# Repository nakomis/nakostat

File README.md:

# Nakostat

## Support

If you find this useful, please consider buying me a coffee:

<!-- toc -->

- [Hardware](#hardware)
- [Architecture](#architecture)
- [Repo layout](#repo-layout)
- [Quick start](#quick-start)
- [Toolchain versions](#toolchain-versions)
- [Lint and format](#lint-and-format)
- [Deployment versions](#deployment-versions)
- [Related repos](#related-repos)
- [Licence](#licence)
- [Support](#support)

<!-- tocstop -->

A DIY smart thermostat built after the Nest thermostat and Heatlink both failed. Replaces both with a Raspberry Pi touch-screen UI, an ESP32 boiler relay controller, AWS IoT Core, and an Alexa thermostat skill.

The heatlink's circuit boards ([`pcb/heatlink/`](pcb/heatlink/)) were manufactured and assembled by
[PCBWay](https://www.pcbway.com), who sponsored the first batch.

## Hardware

| Device | Role |
|--------|------|
| Raspberry Pi 5 + RC070S 7" touch | Touch-screen UI (1024×600, egui) |
| ENS160+AHT21 | Temperature, humidity, CO₂/eCO₂/TVOC |
| ESP32-S3 heatlink | Boiler relay controller (ESP-IDF, Fleet OTA) |
| 3-way rotary switch | Physical override: auto / off / on |
| Amazon Echo | Voice control via Alexa thermostat skill |

## Architecture

```
 Pish (dial, separate repo) ─pish/setpoint─┐
 Web (nakostat.nakomis.com) ─API─► api/{setpoint,mode,schedule} ─┤
 Alexa Smart Home skill ─Lambda─► api/{setpoint,mode} ───────────┤
                                                                 ▼
          Pi sensor daemon (the brain: schedule, override, hysteresis)
             │ demand every 30 s, set_schedule          ▲ status
             ▼                                           │
     nakostat/nakostat-heatlink/commands      …/status, …/responses
             │                                           │
          Heatlink (ESP32-S3, ESP-IDF, Fleet OTA) ── relay ── boiler ROOM STAT/TIMER (230 V)
             ▲
          3-way switch (on / auto / off); falls back to a local schedule if demand stops
```

Contracts (topics, payloads): `docs/superpowers/specs/2026-10-19-heatlink-v2-prototype-design.md`.

## Repo layout

| Directory | Contents |
|-----------|----------|
| `3d/` | Printed enclosure models |
| `docs/` | Architecture diagrams and notes |
| `embedded/pi/` | Rust/egui touch UI and sensor daemon |
| `embedded/esp32/heatlink/` | ESP-IDF heatlink firmware (boiler relay, switch, fallback schedule); see its [README](embedded/esp32/heatlink/README.md) |
| `githooks/` | Pre-commit hooks |
| `infra/` | AWS CDK stacks |
| `pcb/` | PCB designs |
| `scripts/` | Helper scripts |
| `web/` | React dashboard (nakostat.nakomis.com) |

## Quick start

```bash
# Install git hooks
bash scripts/install-hooks.sh
```

## Toolchain versions

Every toolchain is pinned in [`.tool-versions`](.tool-versions), which is the single source of truth for local development and CI:

| Tool | Used by | How CI reads it |
|------|---------|-----------------|
| `nodejs` | `infra/`, `web/` | `actions/setup-node` with `node-version-file: .tool-versions` |
| `pnpm` | `infra/`, `web/` | `pnpm/action-setup` reads `packageManager` in `infra/package.json` and `web/package.json`; the **Toolchain pins** job fails if that disagrees with `.tool-versions` |
| `python` | heatlink host tests (`embedded/esp32/heatlink/tests/`) | `actions/setup-python` with `python-version-file: .tool-versions` |
| `rust` | `embedded/pi/sensor-daemon/` | the `rust` line is passed to `dtolnay/rust-toolchain` |

With [asdf](https://asdf-vm.com/) (`nodejs`, `pnpm`, `python` and `rust` plugins) run `asdf install` in the repo root; with [mise](https://mise.jdx.dev/), `mise install`. The heatlink firmware builds with ESP-IDF 5.5 (installed with Espressif's own `install.sh`, not asdf); its host tests need pytest from [`embedded/esp32/heatlink/tests/requirements.txt`](embedded/esp32/heatlink/tests/requirements.txt).

To bump a tool, change `.tool-versions` (and, for pnpm, `packageManager` in `package.json`) in the same PR.

## Lint and format

CI gates every sub-project on lint and formatting as well as tests. Run the same checks locally before pushing:

```bash
# web/ — Biome lint + format check
cd web && pnpm lint

# infra/ — type-check, then Biome at the version infra/biome.json declares
cd infra && pnpm exec tsc --noEmit && pnpm dlx @biomejs/biome@2.4.16 ci .
# auto-fix formatting and safe lint fixes:
cd infra && pnpm dlx @biomejs/biome@2.4.16 check --write .

# embedded/pi/sensor-daemon/ — rustfmt + clippy
cd embedded/pi/sensor-daemon && cargo fmt --check && cargo clippy --all-targets -- -D warnings
```

Keep the Biome version in `infra/biome.json`'s `$schema` equal to `web/biome.json`'s; the **Toolchain pins** job checks this. The ESP32 firmware has no lint gate yet: it has no `.clang-format`, and `pio check` would download the whole ESP32 toolchain on every run.

## Deployment versions

Infra deploys record their version in the shared nakomis deployment tracker (`api.infra.nakomis.com`, defined in [nakomis-infra](https://github.com/nakomis/nakomis-infra)) under the project key `nakostat-infra`. On a push to `main` the **Compute infra version** job reads the latest sandbox version from the tracker and bumps it — a line that is exactly `--bump-major` or `--bump-minor` in the merged commit message bumps that part, otherwise the patch. The same `infra/version.json` is deployed to sandbox and then prod, and each deploy is recorded after it succeeds. Recording is non-fatal, so a tracker outage never fails a deploy.

## Related repos

- [`rotary-dial`](https://github.com/nakomis/rotary-dial) — egui thermostat dial widget (migrating into `embedded/pi/`)
- [`pish`](https://github.com/nakomis/pish) — the Pi touch-screen shell; its `nakostat` widget is the thermostat dial
- [`nakomis-fleet`](https://github.com/nakomis/nakomis-fleet) — device registry and OTA for the heatlink

## Licence

[CC0 1.0 Universal](LICENSE) — public domain dedication.

## Support

If you find this useful, please consider buying me a coffee:

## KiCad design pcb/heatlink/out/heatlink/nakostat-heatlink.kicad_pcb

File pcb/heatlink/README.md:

# Nakostat heatlink board (STAT-75)

The heatlink on one board: an ESP32-S3-MINI-1 module, a relay on the boiler's 230 V
`ROOM STAT/TIMER` pair, the 3-way override toggle, a WS2812B status LED, and, to make spare boards
reusable, an 8-way IO terminal (power, I²C and three GPIOs) and a 16-way IDC header (twelve more). It is powered over the
house USB cable. The board is generated in code, from the circuit through to the gerbers, using
tinycrypt's pipeline. `DESIGN.md` covers the parts, the circuit and the mains safety rules.

**[The component key](../../docs/heatlink-board-key.md)** explains what every numbered part does, and why it's there. The dashed orange
ring marks where the case needs a vent: above the 3.3 V regulator (U2), the warmest part.

## Build

```bash
ASDF_PYTHON_VERSION=3.11.15 python -m venv .venv
.venv/bin/pip install -r requirements.txt
mkdir -p freerouting && cp <somewhere>/freerouting-2.5.0.jar freerouting/   # Java via asdf (25)
./fetch_parts.sh                       # only if footprints/ is missing or a part is added
.venv/bin/python build.py --route      # full router log: /tmp/claude-501/heatlink-board-route.log
.venv/bin/python -m pytest
```

`build.py` writes these to `out/heatlink/`:

- `nakostat-heatlink.kicad_pcb`, with its `.kicad_pro` and `.kicad_dru` (the mains rules)
- `drc.json`
- `bom-jlcpcb.csv` and `bom-pcbway.csv`
- `cpl.csv`
- `nakostat-heatlink-gerbers.zip`
- the top and bottom renders
- `pins.h`
- `nakostat-heatlink-key.png` and `docs/heatlink-board-key.md` (the text lives in `board/key.py`; after editing it,
  `.venv/bin/python -m board.key` redraws both from the existing render without a rebuild)

It writes the fab files only when KiCad's DRC reports no errors and no unconnected items. Those
checks include the 8 mm mains spacing. `--step` also fetches the 3D models and writes
`nakostat-heatlink.step` and a 3D render, which the case design needs.

## Made by PCBWay (sponsored)

The first five boards (November 2026) were manufactured and assembled by
[PCBWay](https://www.pcbway.com), who sponsored the build: they covered the boards, the parts and the
assembly. The files here aren't tied to them; the same gerbers and placement file, with
`bom-jlcpcb.csv`, also work at JLCPCB.

## Ordering

The same files work for both fabs. Only the BOM differs.

| | PCBWay | JLCPCB |
|---|---|---|
| Gerbers | `nakostat-heatlink-gerbers.zip` | same |
| BOM | `bom-pcbway.csv` (manufacturer + part number) | `bom-jlcpcb.csv` (LCSC numbers) |
| Placement | `cpl.csv` | same |

- 2 layers, 1.6 mm, **ENIG**, **black** mask, white silkscreen.
- Assembly is top side only. Five parts are through-hole: K1 (relay), J2 and J3 (terminal blocks),
  J4 (IDC header) and SW2 (toggle switch).
- The module's antenna **overhangs the board edge by 5.05 mm on purpose**. If the engineering
  review asks, say the overhang is intended.
- The board carries 230 V between J2 and the relay contacts. There is no ground pour in that area,
  and it is marked on both silkscreens.
- Check the rotations of U1, J1, J2, J3, J4, K1 and SW2 in the fab's placement preview.

## Before the first power-up

- **Check the USB cable's pinout with a meter:** 1 VBUS, 2 D−, 3 D+, 4 CC, 5 GND. A reversed VBUS
  trips the resettable fuse, but the data lines have no protection against a wrong cable.
- **Bench-test first with no mains connected.** Use the same steps as the prototype
  (`docs/heatlink-prototype-wiring.md`): the relay should click on demand, and the toggle should
  override it.
- **Wire the boiler with the power off at the spur.** L and SL go to J2 in place of the link wire.
  Fit bootlace ferrules to the flex, and clamp it in the gland so no pull reaches J2.
- **Use nylon screws in the two mains-end holes (H1, H2).** A metal M3 screw and washer in H2 would
  sit about 2.9 mm from J2, inside the board's own 3 mm rule.
- **Use a reputable, certified USB charger.** Its isolation is the real barrier between the mains
  and everything on the low-voltage side, including J3 and J4.
- **Keep loads on J3 and J4 small:** about 100 mA from 3V3 and 150 mA from 5V. The 3V3 regulator
  runs warm at sustained loads, and the 500 mA polyfuse is shared with the relay and the module,
  so a short on a header's 5V pin drops the heating control until it's removed.
- **House it in a flame-retardant enclosure** (UL94 V-0, e.g. a bought ABS or PC box, or a V-0
  filament), not PETG or ASA, because the case holds the 230 V terminals.

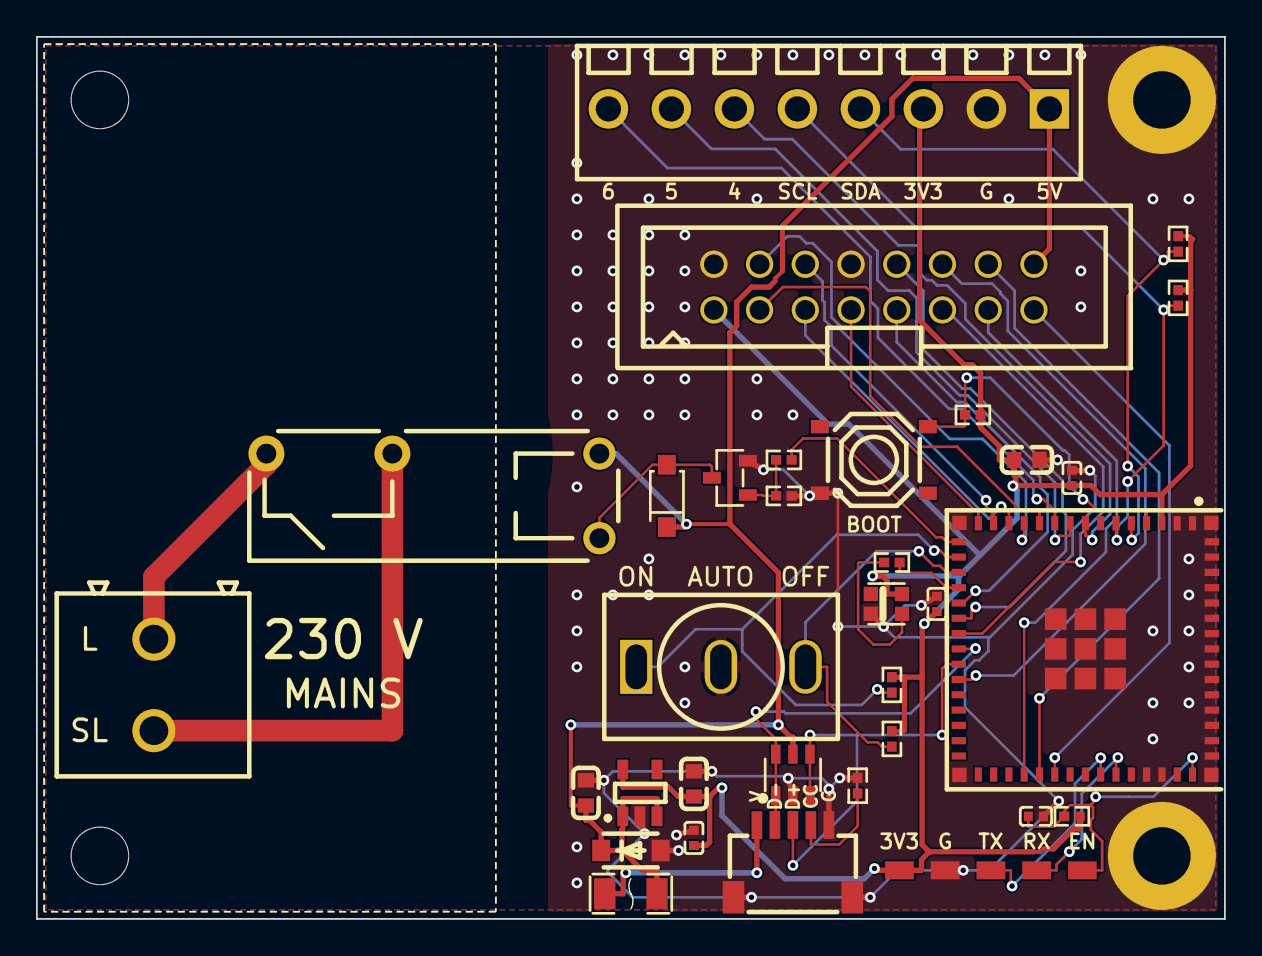
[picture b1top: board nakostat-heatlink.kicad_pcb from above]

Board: 2 copper layers, 66.0 x 49.0 mm, 38 parts (1 on the bottom side), 37 nets.

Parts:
ART1: ART1
C1, C2, C4: 10uF; C0603
C3, C5, C8: 100nF; C0402
C6: 1uF; C0402
D1: WS2812B-2020-V6; LED-SMD_4P-L2.2-W2.0-P1.00_WS2815C-2020-4P
D2: SMF5.0A; SOD-123F_L2.8-W1.8-LS3.7-RD
D3: 1N4148W; SOD-123F_L2.7-W1.6-LS3.8-RD
F1: 500mA PTC; F1206
H1, H2: M3 hole, unplated; MountingHole_M3_3.2mm_NPTH
H3, H4: M3 hole; MountingHole_M3_3.2mm_Pad6
J1: SM05B-SRSS-G-TB; CONN-SMD_SM05B-SRSS-G-TB-LF-SN
J2: KF128-5.08-2P; CONN-TH_P5.08_KF128-5.08-2P
J3: DB125-3.5-8P-GN-S; CONN-TH_8P-P3.50_DORABO_DB125-3.5-8P-GN-S
J4: DC3-2.54-16PAS; IDC-TH_16P-P2.54_C3406
K1: HF46F/5-HS1; RELAY-TH_HF46F-XX-HS1XX-XXX
Q1: AO3400A; SOT-23-3_L2.9-W1.3-P1.90-LS2.4-BR
R1: 5k1; R0402
R2, R3, R9, R10: 10k; R0402
R4, R5: 4k7; R0402
R6: 330R; R0402
R7: 100R; R0402
R8: 100k; R0402
SW1: TS-1187A-B-A-B; SW-SMD_4P-L5.1-W5.1-P3.70-LS6.5-TL_H1.5
SW2: MTS-103 ON-OFF-ON; SW-TH_MT-0-103-A101-M200-RS
TP1: Debug pads; DebugPads_1x5_P2.54
U1: ESP32-S3-MINI-1-N8; BULETM-SMD_ESP32-S3-MINI-1-N8
U2: AP2112K-3.3TRG1; SOT-25-5_L2.9-W1.6-P0.95-LS2.8-BL
U3: USBLC6-2SC6; SOT-23-6_L2.9-W1.6-P0.95-LS2.8-BL

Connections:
+3V3: C2.1, C3.1, C4.1, C5.1, C8.1, D1.4, J3.3, J4.1, R2.2, R3.2, R4.2, R5.2, R9.2, R10.2, TP1.5, U1.3, U2.5
BUTTON: R3.1, SW1.2, U1.4
CC: J1.4, R1.1
COIL: D3.2, K1.2, Q1.3
EN: C6.1, R2.1, TP1.1, U1.45
GND: C1.2, C2.2, C3.2, C4.2, C5.2, C6.2, C8.2, D1.2, D2.2, H3.1, H4.1, J1.5, J1.6, J1.7, J3.2, J4.2, J4.8, Q1.2, R1.2, R8.2, SW1.3, SW2.2, TP1.4, U1.1, U1.2, U1.42, U1.43, U1.46, U1.47, U1.48, U1.49, U1.50, U1.51, U1.52, U1.53, U1.54, U1.55, U1.56, U1.57, U1.58, U1.59, U1.60, U1.GND, U2.2, U3.2
HDR_7: J4.3, U1.11
HDR_8: J4.4, U1.12
HDR_9: J4.5, U1.13
HDR_10: J4.6, U1.14
HDR_11: J4.7, U1.15
HDR_16: J4.9, U1.20
HDR_17: J4.10, U1.21
HDR_18: J4.11, U1.22
HDR_21: J4.12, U1.25
HDR_38: J4.13, U1.34
HDR_39: J4.14, U1.35
HDR_40: J4.15, U1.36
IO_4: J3.6, U1.8
IO_5: J3.7, U1.9
IO_6: J3.8, U1.10
IO_SCL: J3.5, R5.1, U1.6
IO_SDA: J3.4, R4.1, U1.5
LED: R6.2, U1.19
LED_DIN: D1.3, R6.1
MAINS_L: J2.2, K1.4
MAINS_SL: J2.1, K1.3
RELAY: R7.2, U1.16
RELAY_G: Q1.1, R7.1, R8.1
SW_OFF: R10.1, SW2.3, U1.18
SW_ON: R9.1, SW2.1, U1.17
UART_RX: TP1.2, U1.40
UART_TX: TP1.3, U1.39
USB_DM: J1.2, U1.23, U3.1, U3.6
USB_DP: J1.3, U1.24, U3.3, U3.4
VBUS: C1.1, D2.1, D3.1, F1.2, J3.1, J4.16, K1.1, U2.1, U2.3, U3.5
VBUS_IN: F1.1, J1.1

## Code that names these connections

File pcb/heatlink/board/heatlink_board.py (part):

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ANTENNA = -ESP32_ANTENNA[1] + ESP32_ANTENNA[3]   # 5.05 mm of overhang
MAINS_X = 28.5                         # low-voltage copper stays right of this line (8 mm rule + margin)

# GPIO choice. USB is fixed by the silicon; the relay, switch and LED take the module's inner
# edge (pads 16-19, which face the rest of the board); the button keeps GPIO0 (download strap).
# None is a strapping pin (3/45/46), a flash pin (26-32), an eFuse-dependent SPI pin (33-37) or
# an octal pin (47/48). At reset every one of them is an input, so the relay FET's 100k
# pull-down holds the relay off until the firmware drives it.
GPIO = {"RELAY": 12, "SW_ON": 13, "SW_OFF": 14, "LED": 15, "BUTTON": 0, "USB_DM": 19, "USB_DP": 20,
        "UART_TX": 43, "UART_RX": 44, "IO_SDA": 1, "IO_SCL": 2, "IO_4": 4, "IO_5": 5, "IO_6": 6,
        **{f"HDR_{n}": n for n in (7, 8, 9, 10, 11, 16, 17, 18, 21, 38, 39, 40)}}
_MODPIN = {43: "TXD0", 44: "RXD0"}
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

# J1 (house USB, tinycrypt's J1): 1 VBUS, 2 D-, 3 D+, 4 CC, 5 GND; pads 6/7 are the shell tabs.
J1_PINS = {"1": "VBUS_IN", "2": "USB_DM", "3": "USB_DP", "4": "CC", "5": "GND"}
J1_LABELS = {"1": "V", "2": "D-", "3": "D+", "4": "CC", "5": "G"}
# J2 (boiler): the permanent live in, and the switched live back to the boiler. The relay just
# joins them, so the order does not matter electrically; the labels match the boiler's wiring.
J2_PINS = {"2": "MAINS_L", "1": "MAINS_SL"}
J2_LABELS = {"2": "L", "1": "SL"}
DEBUG_PINS = {"1": "EN", "2": "UART_RX", "3": "UART_TX", "4": "GND", "5": "+3V3"}
DEBUG_LABELS = {"1": "EN", "2": "RX", "3": "TX", "4": "G", "5": "3V3"}
# J3 (IO terminal, for reuse): 5V at one end, so a stray strand from it can reach only GND (and
# the PTC limits that); 3V3 beside a GPIO does no harm. SDA/SCL have 4.7k pull-ups to 3V3. The
# GPIOs go straight to the module, as on a dev board. All five are ADC1 pins.
IO_PINS = {"1": "VBUS", "2": "GND", "3": "+3V3", "4": "IO_SDA", "5": "IO_SCL", "6": "IO_4", "7": "IO_5",
           "8": "IO_6"}
IO_LABELS = {"1": "5V", "2": "G", "3": "3V3", "4": "SDA", "5": "SCL", "6": "4", "7": "5", "8": "6"}
# J4 (16-way boxed IDC header, 2.54 mm): a ground between the signal groups, as ribbon practice
# has it; 3V3 and GND at pin 1-2, 5V at pin 16. Odd pins are the row on the key side.
HDR_PINS = {"1": "+3V3", "2": "GND", "3": "HDR_7", "4": "HDR_8", "5": "HDR_9", "6": "HDR_10",
            "7": "HDR_11", "8": "GND", "9": "HDR_16", "10": "HDR_17", "11": "HDR_18", "12": "HDR_21",
            "13": "HDR_38", "14": "HDR_39", "15": "HDR_40", "16": "VBUS"}
HDR_LABELS = {n: {"+3V3": "3V3", "GND": "G", "VBUS": "5V"}.get(net, net[4:]) for n, net in HDR_PINS.items()}
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    c.connect("VBUS_IN", (f1, "1"))
    c.connect(vbus, (f1, "2"), (d2, "1"))            # D2 pad 1 = cathode
    c.connect(gnd, (d2, "2"))
    c.connect("USB_DM", (u3, "1"), (u3, "6"), (u1, modpin(GPIO["USB_DM"])))
    c.connect("USB_DP", (u3, "3"), (u3, "4"), (u1, modpin(GPIO["USB_DP"])))
    c.connect(vbus, (u3, "5"))
    c.connect(gnd, (u3, "2"))
    c.connect("CC", (c.add("R5K1", "R1"), "1"))
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    c.connect(gnd, (q1, "S"))
    r7, r8 = c.add("R100", "R7"), c.add("R100K", "R8")
    c.connect("RELAY_G", (q1, "G"), (r7, "1"), (r8, "1"))
    c.connect("RELAY", (r7, "2"), (u1, modpin(GPIO["RELAY"])))
    c.connect(gnd, (r8, "2"))
    for pad, net in J2_PINS.items():
        c.connect(net, (j2, pad))
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    # 3-way toggle (ON-OFF-ON): common (2) to GND, each throw to a GPIO with a 10k pull-up. The
    # middle position (neither throw) is auto.
    c.connect(gnd, (sw2, "2"))
    c.connect("SW_ON", (sw2, "1"), (u1, modpin(GPIO["SW_ON"])), (c.add("R10K", "R9"), "1"))
    c.connect("SW_OFF", (sw2, "3"), (u1, modpin(GPIO["SW_OFF"])), (c.add("R10K", "R10"), "1"))
    c.connect(v33, (c.instances["R9"], "2"), (c.instances["R10"], "2"))

    # WS2812B-2020: VDD 3V3 + 100 nF, DIN from a GPIO through 330R, DOUT unconnected.
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    cap("C100N", "C8", v33)

    # Debug pads: EN, UART0 (GPIO43/44), GND, 3V3.
    c.connect("UART_TX", (u1, modpin(GPIO["UART_TX"])))
    c.connect("UART_RX", (u1, modpin(GPIO["UART_RX"])))
    for pad, net in DEBUG_PINS.items():
        c.connect(net, (tp, pad))

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
def mains_hand_route():
    """(tracks, vias) for the two mains nets, F.Cu only: J2 -> relay contacts. MAINS_L runs up
    from J2's upper pin and across to pad 4; MAINS_SL along y = J2's lower pin to x of pad 3,
    then up. They stay at least MAINS_FUNCTIONAL apart."""
    _KEY.update({"J2": "TERM", "K1": "RELAY"})
    jl, jsl = pad_xy("J2", "2"), pad_xy("J2", "1")
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    h = Image.open(ART_PNG).size[1]
    holes = [(AT[r][0], AT[r][1], HOLE_CLEAR) for r in ("H3", "H4")]
    # and the through-hole pads that come through to the back under her: the toggle's three and
    # the relay's coil pins (silk over a pad is clipped by the fab anyway)
    _KEY.update({"SW2": "TOGGLE", "K1": "RELAY"})
    holes += [(*pad_xy("SW2", n), 1.9) for n in "123"] + [(*pad_xy("K1", n), 1.3) for n in "12"]
    return [(ART_PNG, ART_X, ART_TOP, round(h * ART_PX, 3), "back", holes)]
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
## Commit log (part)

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2026-04-24 chore: scaffold nakostat monorepo
    Directory structure, gitignore, README, CLAUDE.md, githooks, and scripts
    matching the bootboots project layout.
2026-04-24 chore: add CI, licence, updated README, and test-first policy
    - CC0 LICENSE
    - README with Support/donate section at top and bottom
    - CLAUDE.md: test-first approach, 70% coverage policy, per-language tooling
    - GitHub Actions CI: Rust/llvm-cov, CDK/Jest, React/Vitest+Playwright, ESP32/PlatformIO native
    Each job skips gracefully when the sub-project directory is empty
2026-04-25 refactor(infra): move nakostat CI role definition into GithubCiStack
2026-04-25 feat(ci): add CDK synth, sandbox and prod deploy jobs
2026-04-25 fix(ci): check out post-merge ref on PRs to test what will land on main
2026-04-26 feat(web): CloudFront SPA hosting and Cognito client for nakostat (NAKO-22)
    - WebCertStack: ACM cert for nakostat.{domain} in us-east-1 (CloudFront requirement)
    - WebStack: S3 bucket + CloudFront distribution with OAC, SPA 404→index.html routing,
    Cognito UserPoolClient referencing shared nakomis-infra pool via SSM,
    Route53 A+AAAA aliases for nakostat.sandbox.nakomis.com / nakostat.nakomis.com
    - Client ID published to SSM at /nakostat/{env}/cognito/client-id
    - 55 tests, 100% coverage
2026-04-26 feat(web): add One Dark managed login branding for nakostat client (NAKO-22)
    CloudFormation requires a clientId on CfnManagedLoginBranding, so branding
    lives here in WebStack tied to the nakostat-{env} client rather than in
    the shared AuthStack.
2026-04-26 fix(ci): bump all Node versions to 25 to match local toolchain
2026-04-26 chore(web): add open-source notice comment to index.html
2026-04-26 fix(web): remove webServer from playwright config, pass-with-no-tests in CI
2026-04-26 fix(web): add type declarations for PNG and SVG image imports
2026-04-26 fix(web): don't override OIDC credentials with AWS_PROFILE in CI
2026-04-26 fix(web): read region from env var before falling back to aws configure
2026-04-26 ci(web): verify set-config.sh against sandbox AWS in PR checks
2026-04-27 feat(web): add favicon set and webmanifest (NAKO-33)
2026-04-27 feat(infra+web): IoT rules, HTTP API, and current state panel (NAKO-30, NAKO-21, NAKO-26)
    - IotRulesStack: IoT Topic Rules routing pi/readings and esp32/status MQTT to Lambda → DynamoDB
    - ApiStack: HTTP API Gateway v2 with GET /state and GET /readings endpoints, CORS, SSM-published URL
    - CurrentStatePanel: React MUI card fetching thermostat state from the API
    - config template and set-config.sh updated to include apiUrl (graceful fallback if not yet deployed)
2026-04-27 fix(ci): always run sensor-daemon job — path filter was broken
    The if-condition used github.event.pull_request.changed_files_url which
    is an API URL, not a file path list, so contains('embedded/pi') always
    evaluated false and skipped the job on every PR.
2026-04-27 Revert "fix(ci): exclude main.rs from coverage — binary entry point is not unit-testable"
    This reverts commit e5166499ca194c7066a02e5f58c282c8feca8ac6.
2026-04-27 test(pi): add coverage for MqttPublisher error paths (NAKO-17)
    Tests for sink error propagation and MqttPublisher::new failure modes
    (missing cert, missing key, no private key in PEM) bring mqtt.rs
    coverage above 70%, satisfying the CI threshold without excluding files.
2026-04-27 ci: skip ESP32 job gracefully when project not yet initialised (NAKO-17)
2026-04-27 ci: add CI Status gatekeeper job for path-filtered checks
2026-04-27 feat(infra): API Gateway Cognito authoriser and write endpoints (NAKO-35)
    Add JWT authentication via Cognito UserPool authoriser to all API routes.
    Implement POST /setpoint handler to update boiler heating setpoint and publish
    MQTT notifications with user tracking. Implement GET /boiler-usage handler to
    query boiler on/off history with date range and source filtering. Add DynamoDB
    table (nakostat-boiler-usage-{env}) with TTL for automatic 1-year retention.
    Include comprehensive unit tests (70%+ coverage) with aws-sdk-client-mock.
2026-04-27 Trigger CI with new gatekeeper job
2026-04-27 chore(infra): update lock file for IoT Data Plane SDK
2026-04-27 fix(infra): resolve Jest/AWS SDK ESM compatibility and mock issues (NAKO-35)
    @aws-sdk/xml-builder v3.972.20 introduced @nodable/entities (pure ESM, no CJS
    build), breaking Jest's CJS runner with 'Unexpected token export'.
    Fixes:
    - Pin @aws-sdk/xml-builder to 3.972.19 via npm overrides (last version without
    @nodable/entities dependency)
    - Add transformIgnorePatterns to allow Jest to transform @aws-sdk, @smithy, and
2026-04-27 feat(infra): API Gateway Cognito authoriser and write endpoints (NAKO-35) (#20)
    * ci: add CI Status gatekeeper job for path-filtered checks
    * feat(infra): API Gateway Cognito authoriser and write endpoints (NAKO-35)
    Add JWT authentication via Cognito UserPool authoriser to all API routes.
    Implement POST /setpoint handler to update boiler heating setpoint and publish
    MQTT notifications with user tracking. Implement GET /boiler-usage handler to
    query boiler on/off history with date range and source filtering. Add DynamoDB
2026-05-03 Adds icons (#21)
2026-05-06 feat(boiler): add nakostat-boiler ESP32 firmware (STAT-13)
    Generated from esp32-bootstrap @ main with:
    - core libs: SDLogger, WifiConnect, BluetoothOTA, OTAUpdate
    - AWSAuth (SigV4 signing, credentials provider)
    - certificates scripts
    Lands at embedded/esp32/boiler/. Builds cleanly:
    pio run -e esp32s3_n16r8
2026-05-06 feat(boiler): MQTT setpoint control + relay watchdog
    First cut of the closed-loop boiler controller. Pi-side controller
    publishes thin commands ({"on": true|false}) on
    nakostat/{env}/esp32/command; ESP32 drives a relay GPIO accordingly
    and publishes JSON status on nakostat/{env}/esp32/status (on every
    command, on connect, on watchdog trip, plus a 30s heartbeat).
    - New BoilerController library wraps relay GPIO + watchdog. If no
2026-06-02 feat(pi): hard-coded heating schedule drives the setpoint (STAT-45) (#24)
    Add a schedule module to the sensor daemon: a weekly
    Map<DayOfWeek, List<ScheduleEntry>> of transition points, evaluated
    against the local wall clock to produce the current setpoint. Entries
    carry over across midnight and wrap around the week, so early-morning
    hours inherit the previous night's setback. The MVP schedule is
    hard-coded; the data shape matches STAT-46 so later stories swap the
2026-06-02 feat(infra): secure HTTP API with Cognito authoriser + wire write endpoints (STAT-41)
    PR #20 added the setpoint and boiler-usage handler Lambdas but never wired the
    API Gateway: no authoriser, the write endpoints were never routed, and GET
    /state and GET /readings were left open. This completes that work.
    - Add an HttpJwtAuthorizer (shared NakomisUserPool issuer, nakostat client
    audience) as the API default authoriser, so /state and /readings now require
    a valid Cognito JWT.
2026-06-02 feat(web): send Cognito Bearer token on dashboard API calls (STAT-41)
    The /state route is now behind the HTTP API's Cognito JWT authoriser, so
    the dashboard must present its access token. CurrentStatePanel gains an
    optional accessToken prop and sends Authorization: Bearer <token> when
    present; HomePage sources the token from the react-oidc-context session.
2026-06-03 feat(web): bootstrap greenfield Vite app, replacing CRA (STAT-53)
    Rebuild the web dashboard toolchain from scratch on modern foundations,
    retiring Create React App (deprecated/unmaintained, pinned TypeScript 4.9).
    - Vite 8 + React 19 + TypeScript 6 (strict)
    - Vitest 4 + Testing Library for unit/component tests (70% coverage gate)
    - Biome for lint + format (replaces ESLint/Prettier)
    - zod 4 available for the typed API layer (STAT-56)
2026-06-03 fix(web): pin lockfile to public npm registry, not the home Nexus
    The lockfile was generated on a Nexus-configured machine, so every
    resolved: URL pointed at packages.home.nakomis.com (the mTLS-gated home
    proxy). GitHub CI has no client cert, so npm ci got 401 from nginx.
    Rewrite the resolved hosts back to registry.npmjs.org to match the infra
    and (old) web lockfiles. Nexus is a transparent proxy, so the tarballs are
    byte-identical and every integrity hash is preserved.
2026-06-03 feat(web): adopt Tailwind v4 + shadcn/ui component system (STAT-54)
    Replace the placeholder styling with the project's component system.
    - Tailwind CSS v4 via @tailwindcss/vite (CSS-first config, no PostCSS)
    - shadcn/ui (Radix primitives, radix-nova preset) initialised; @/ alias
    wired in vite.config, tsconfig, and components.json
    - Base primitives: button, card, badge, skeleton + a small Spinner
    - Dark by default (<html class="dark">), theme tokens in index.css
2026-06-03 docs(web): explain how Vite/Tailwind/shadcn/Radix fit together
    Add web/components.md: a map of what each tool is responsible for, the
    Radix (behaviour) vs Tailwind (looks) vs shadcn (assembled, owned) split,
    and a build-time/run-time trace. Reference for cloning this as a template.
2026-06-03 docs(web): explain how Vite/Tailwind/shadcn/Radix fit together (#29)
    Add web/components.md: a map of what each tool is responsible for, the
    Radix (behaviour) vs Tailwind (looks) vs shadcn (assembled, owned) split,
    and a build-time/run-time trace. Reference for cloning this as a template.
2026-06-03 feat(web): migrate to pnpm for a registry-agnostic lockfile (STAT-64)
    npm bakes the absolute resolved tarball URL (host + /repository/npm-proxy/
    path) into package-lock.json. On a dev machine the global ~/.npmrc points at
    the home Nexus proxy, so those URLs get baked in and CI's npm ci 401s (no mTLS
    client cert). The interim workaround was a brittle manual sed after every
    dependency change.
    pnpm's lockfile stores resolution: {integrity: <sha512>} only — no host, no
2026-06-03 feat(web): migrate to pnpm for a registry-agnostic lockfile (STAT-64) (#31)
    npm bakes the absolute resolved tarball URL (host + /repository/npm-proxy/
    path) into package-lock.json. On a dev machine the global ~/.npmrc points at
    the home Nexus proxy, so those URLs get baked in and CI's npm ci 401s (no mTLS
    client cert). The interim workaround was a brittle manual sed after every
    dependency change.
    pnpm's lockfile stores resolution: {integrity: <sha512>} only — no host, no
2026-06-03 feat(web): migrate to pnpm for a registry-agnostic lockfile (STAT-64) (#32)
    npm bakes the absolute resolved tarball URL (host + /repository/npm-proxy/
    path) into package-lock.json. On a dev machine the global ~/.npmrc points at
    the home Nexus proxy, so those URLs get baked in and CI's npm ci 401s (no mTLS
    client cert). The interim workaround was a brittle manual sed after every
    dependency change.
    pnpm's lockfile stores resolution: {integrity: <sha512>} only — no host, no
